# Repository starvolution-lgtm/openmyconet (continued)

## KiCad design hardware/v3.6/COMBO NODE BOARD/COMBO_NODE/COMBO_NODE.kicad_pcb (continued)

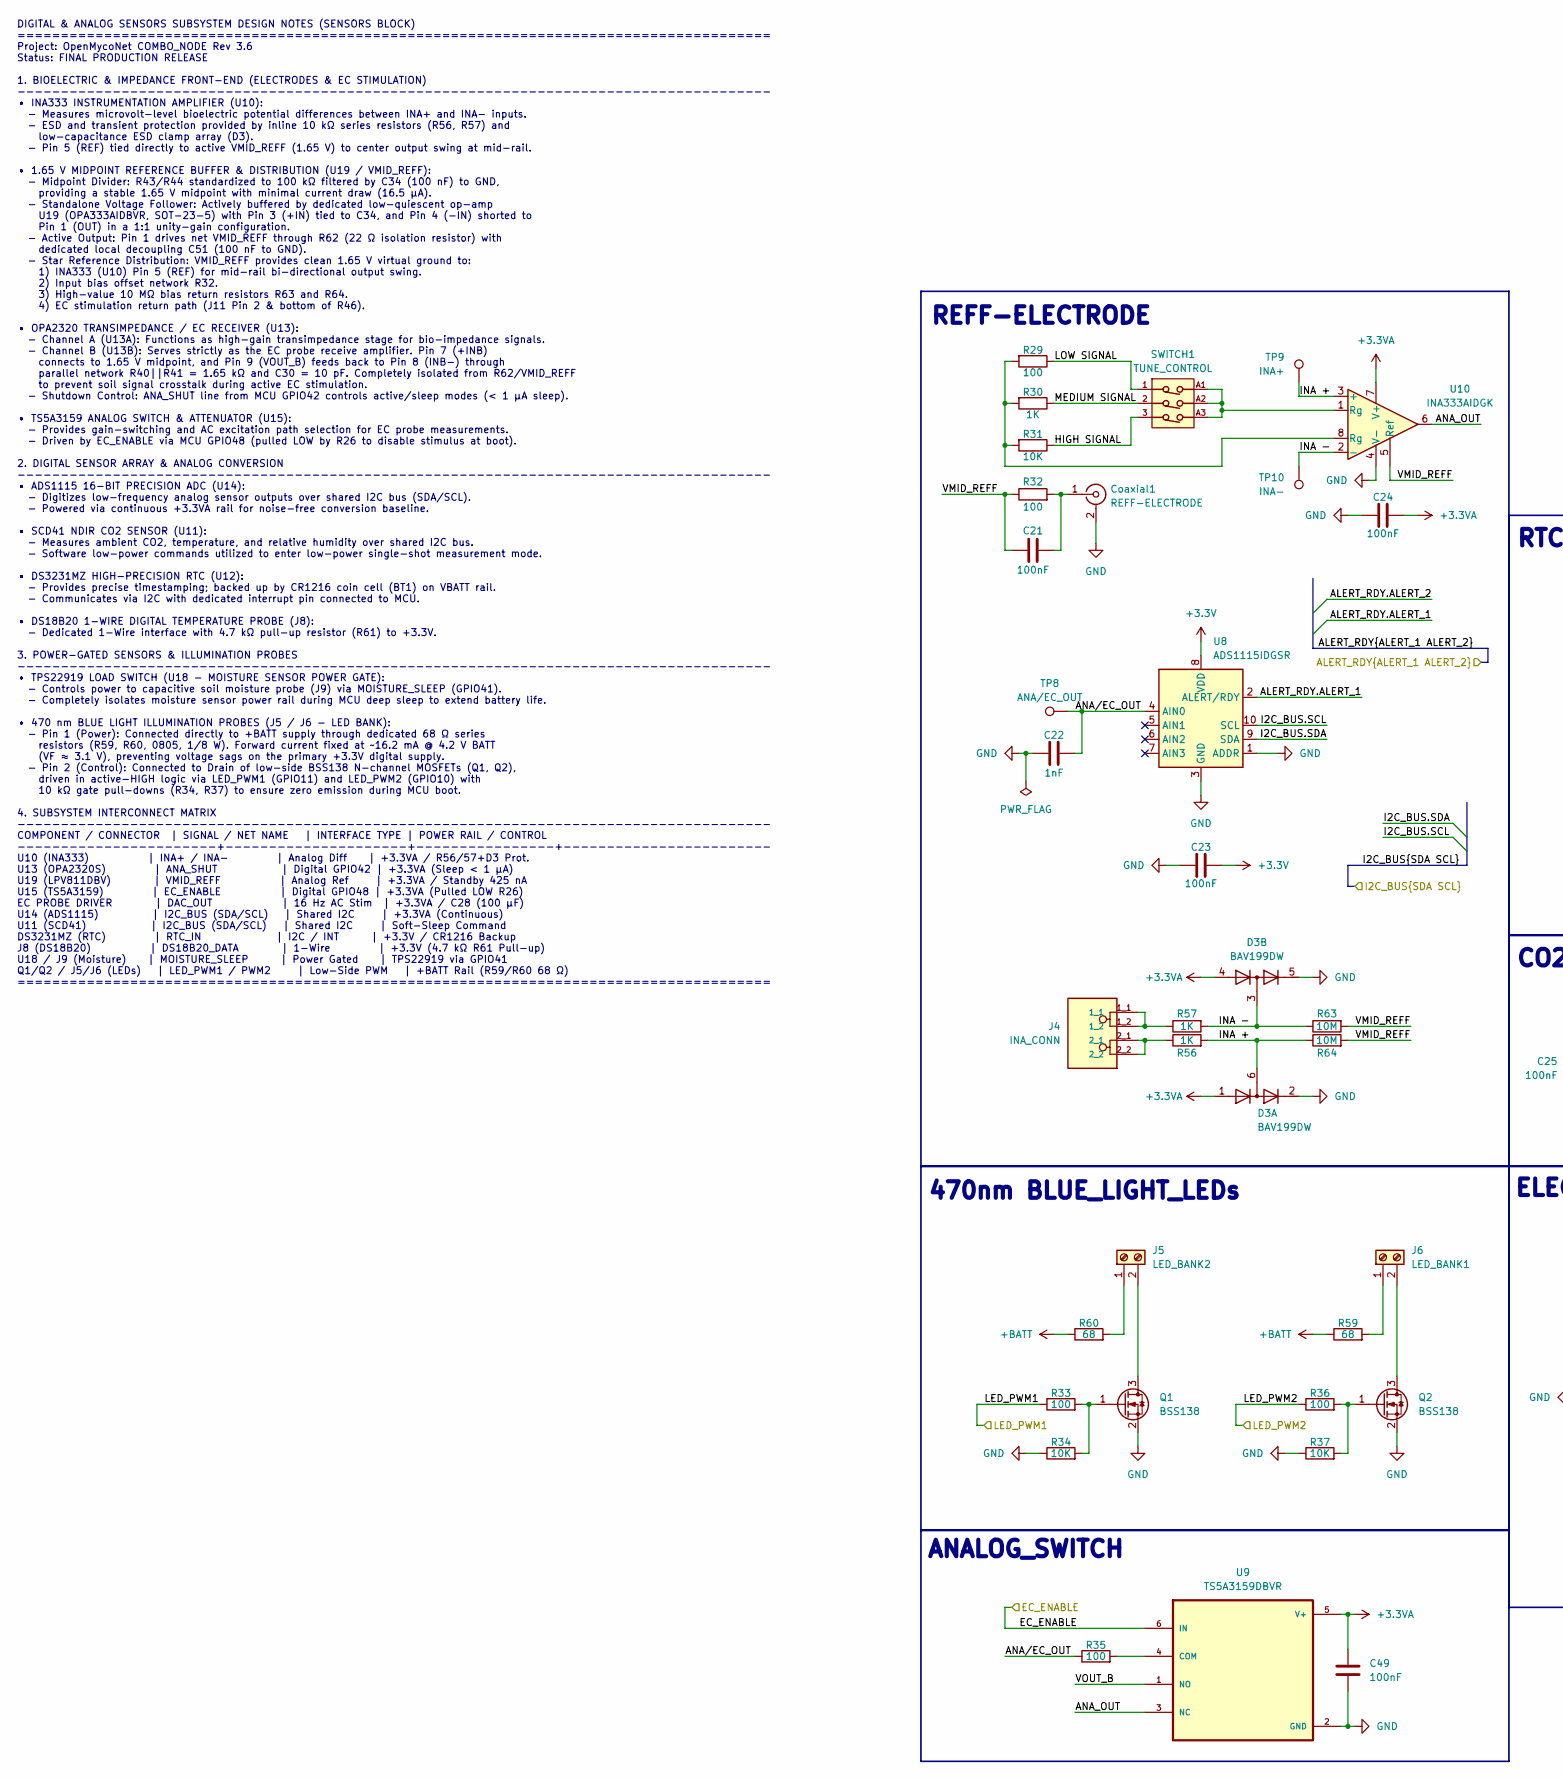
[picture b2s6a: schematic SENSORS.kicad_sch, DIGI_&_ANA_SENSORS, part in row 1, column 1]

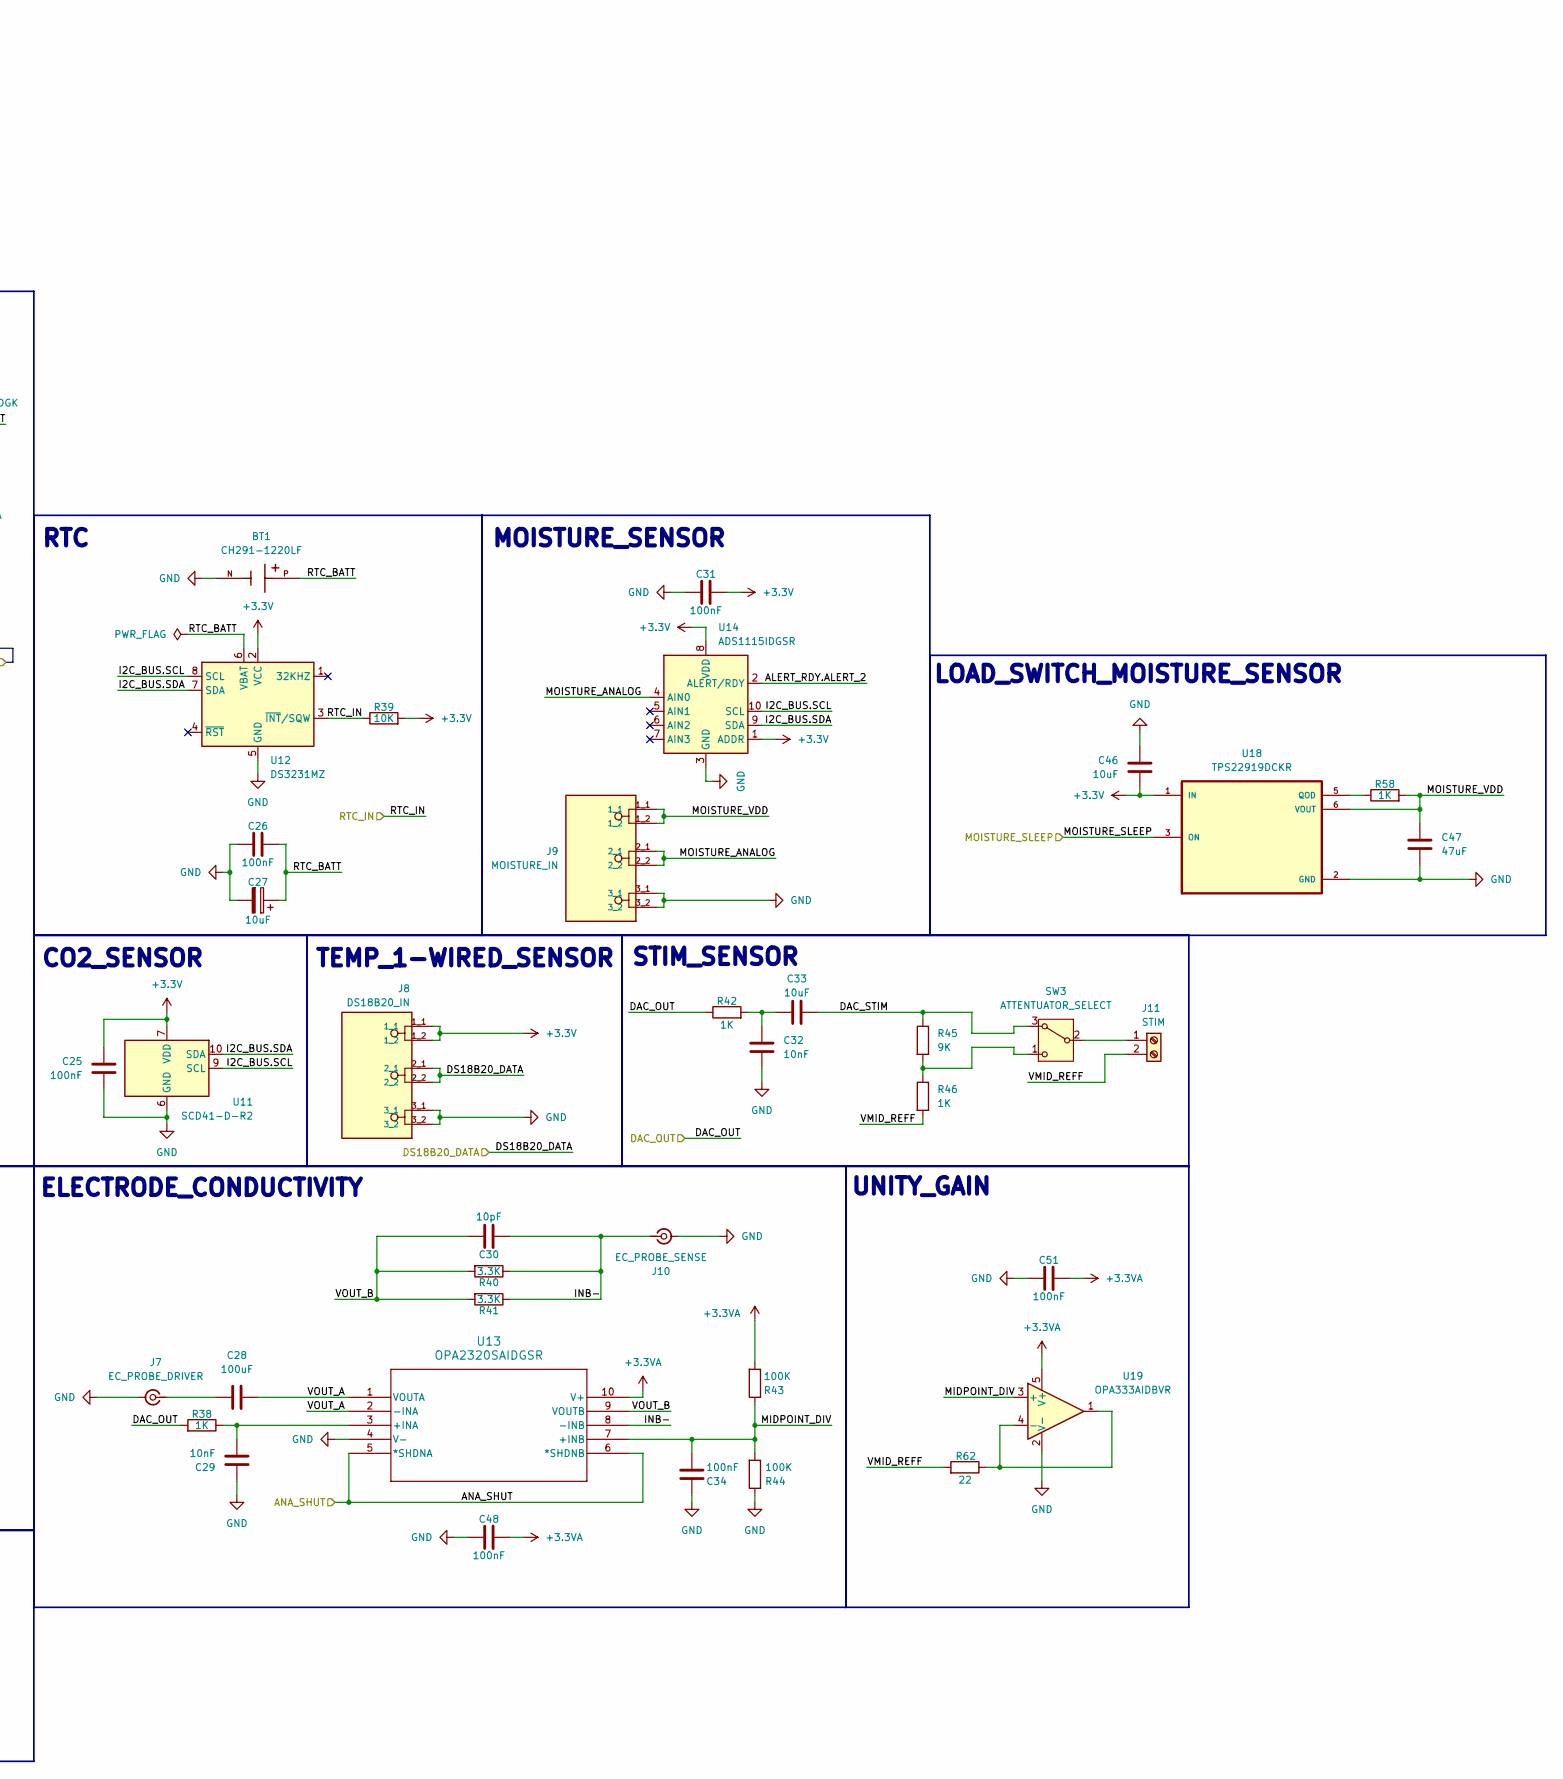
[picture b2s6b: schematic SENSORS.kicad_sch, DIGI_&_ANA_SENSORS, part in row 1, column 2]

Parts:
BT1: CH291-1220LF; BAT_CH291-1220LF; PARTREV A
C21, C25: 100nF; C_0805_2012Metric
C22: 1nF; C_0603_1608Metric
C23, C24, C26, C31, C34, C48, C49, C51: 100nF; C_0603_1608Metric
C27: 10uF; CP_EIA-3216-18_Kemet-A
C28: 100uF; C_1206_3216Metric
C29, C32: 10nF; C_0805_2012Metric
C30: 10pF; C_0603_1608Metric
C33: 10uF; C_0805_2012Metric
C46: 10uF; C_0603_1608Metric
C47: 47uF; C_0603_1608Metric
Coaxial1: REFF-ELECTRODE; CONN_73137-5003_MOL
D3: BAV199DW; SOT-363_SC-70-6
J4: INA_CONN; PHOENIX_1789618; PARTREV 25.11.2016
J5: LED_BANK2; TerminalBlock_Phoenix_MPT-0,5-2-2.54_1x02_P2.54mm_Horizontal
J6: LED_BANK1; TerminalBlock_Phoenix_MPT-0,5-2-2.54_1x02_P2.54mm_Horizontal
J7: EC_PROBE_DRIVER; CONN_73137-5003_MOL
J8: DS18B20_IN; PHOENIX_1790296
J9: MOISTURE_IN; PHOENIX_1790296
J10: EC_PROBE_SENSE; CONN_73137-5003_MOL
J11: STIM; TerminalBlock_Phoenix_MPT-0,5-2-2.54_1x02_P2.54mm_Horizontal
Q1, Q2: BSS138; SOT-23
R29, R32, R33, R36: 100; R_0805_2012Metric
R30, R42, R56, R57: 1K; R_0805_2012Metric
R31, R34, R37, R39: 10K; R_0805_2012Metric
R35: 100; R_0603_1608Metric
R38, R46, R58: 1K; R_0603_1608Metric
R40, R41: 3.3K; R_0603_1608Metric
R43, R44: 100K; R_0603_1608Metric
R45: 9K; R_0603_1608Metric
R59, R60: 68; R_0805_2012Metric
R62: 22; R_0603_1608Metric
R63, R64: 10M; R_0805_2012Metric
SW3: ATTENTUATOR_SELECT; SW_JS102011JCQN
SWITCH1: TUNE_CONTROL; 418117270903
TP8: ANA/EC_OUT; TestPoint_Loop_D1.80mm_Drill1.0mm_Beaded
TP9: INA+; TestPoint_Loop_D1.80mm_Drill1.0mm_Beaded
TP10: INA-; TestPoint_Loop_D1.80mm_Drill1.0mm_Beaded
U8, U14: ADS1115IDGSR; TSSOP-10_3x3mm_P0.5mm; LCSC C37593
U9: TS5A3159DBVR; SOT95P280X145-6N
U10: INA333AIDGK; VSSOP-8_3x3mm_P0.65mm
U11: SCD41-D-R2; Sensirion_SCD4x-1EP_10.1x10.1mm_P1.25mm_EP4.8x4.8mm
U12: DS3231MZ; SOIC-8_3.9x4.9mm_P1.27mm
U13: OPA2320SAIDGSR; DGS10_TEX
U18: TPS22919DCKR; SOT65P210X110-6N
U19: OPA333AIDBVR; SOT-23-5

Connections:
+3.3V: C23.1, C25.1, C31.1, C46.2, J8.1_1, J8.1_2, R39.2, U8.8 (VDD), U11.7 (VDD), U11.19 (VDD), U12.2 (VCC), U14.1 (ADDR), U14.8 (VDD), U18.1 (IN); also elsewhere on the board
+3.3VA: C24.1, C48.1, C49.1, C51.1, D3.1 (A1), D3.4 (A3), R43.2, U9.5 (V+), U10.7 (V+), U13.10 (V+), U19.5 (V+); also elsewhere on the board
+BATT: R59.1, R60.1; also elsewhere on the board
/BLOCK_DIAGRAM/BATTERY/I2C_BUS.SCL: U8.10 (SCL), U11.9 (SCL), U12.8 (SCL), U14.10 (SCL); also elsewhere on the board
/BLOCK_DIAGRAM/BATTERY/I2C_BUS.SDA: U8.9 (SDA), U11.10 (SDA), U12.7 (SDA), U14.9 (SDA); also elsewhere on the board
/BLOCK_DIAGRAM/DIGI_&_ANA_SENSORS/ALERT_RDY.ALERT_1: U8.2 (ALERT/RDY); also elsewhere on the board
/BLOCK_DIAGRAM/DIGI_&_ANA_SENSORS/ALERT_RDY.ALERT_2: U14.2 (ALERT/RDY); also elsewhere on the board
/BLOCK_DIAGRAM/DIGI_&_ANA_SENSORS/ANA_OUT: U9.3 (NC), U10.6
/BLOCK_DIAGRAM/DIGI_&_ANA_SENSORS/ANA_SHUT: U13.5 (*SHDNA), U13.6 (*SHDNB); also elsewhere on the board
/BLOCK_DIAGRAM/DIGI_&_ANA_SENSORS/ANA/EC_OUT: C22.2, R35.1, TP8.1 (1_1), U8.4 (AIN0)
/BLOCK_DIAGRAM/DIGI_&_ANA_SENSORS/DAC_OUT: R38.2, R42.1; also elsewhere on the board
/BLOCK_DIAGRAM/DIGI_&_ANA_SENSORS/DAC_STIM: C33.2, R45.1, SW3.3 (A)
/BLOCK_DIAGRAM/DIGI_&_ANA_SENSORS/DS18B20_DATA: J8.2_1, J8.2_2; also elsewhere on the board
/BLOCK_DIAGRAM/DIGI_&_ANA_SENSORS/EC_ENABLE: U9.6 (IN); also elsewhere on the board
/BLOCK_DIAGRAM/DIGI_&_ANA_SENSORS/HIGH SIGNAL: R31.1, SWITCH1.3
/BLOCK_DIAGRAM/DIGI_&_ANA_SENSORS/INA +: D3.6 (K3A4), R56.2, R64.1, TP9.1 (1_1), U10.3 (+)
/BLOCK_DIAGRAM/DIGI_&_ANA_SENSORS/INA -: D3.3 (K1A2), R57.2, R63.1, TP10.1 (1_1), U10.2 (-)
/BLOCK_DIAGRAM/DIGI_&_ANA_SENSORS/INB-: C30.1, J10.1 (In), R40.1, R41.1, U13.8 (-INB)
/BLOCK_DIAGRAM/DIGI_&_ANA_SENSORS/LED_PWM1: R33.1; also elsewhere on the board
/BLOCK_DIAGRAM/DIGI_&_ANA_SENSORS/LED_PWM2: R36.1; also elsewhere on the board
/BLOCK_DIAGRAM/DIGI_&_ANA_SENSORS/LOW SIGNAL: R29.1, SWITCH1.1
/BLOCK_DIAGRAM/DIGI_&_ANA_SENSORS/MEDIUM SIGNAL: R30.1, SWITCH1.2
/BLOCK_DIAGRAM/DIGI_&_ANA_SENSORS/MIDPOINT_DIV: C34.2, R43.1, R44.2, U13.7 (+INB), U19.3 (+)
/BLOCK_DIAGRAM/DIGI_&_ANA_SENSORS/MOISTURE_ANALOG: J9.2_1, J9.2_2, U14.4 (AIN0)
/BLOCK_DIAGRAM/DIGI_&_ANA_SENSORS/MOISTURE_SLEEP: U18.3 (ON); also elsewhere on the board
/BLOCK_DIAGRAM/DIGI_&_ANA_SENSORS/MOISTURE_VDD: C47.1, J9.1_1, J9.1_2, R58.2, U18.6 (VOUT)
/BLOCK_DIAGRAM/DIGI_&_ANA_SENSORS/RTC_BATT: BT1.P, C26.2, C27.1, U12.6 (VBAT)
/BLOCK_DIAGRAM/DIGI_&_ANA_SENSORS/RTC_IN: R39.1, U12.3 (~INT/SQW); also elsewhere on the board
/BLOCK_DIAGRAM/DIGI_&_ANA_SENSORS/VMID_REFF: C21.1, J11.2, R32.1, R46.2, R62.2, R63.2, R64.2, U10.5 (Ref)
/BLOCK_DIAGRAM/DIGI_&_ANA_SENSORS/VOUT_A: C28.1, U13.1 (VOUTA), U13.2 (-INA)
/BLOCK_DIAGRAM/DIGI_&_ANA_SENSORS/VOUT_B: C30.2, R40.2, R41.2, U9.1 (NO), U13.9 (VOUTB)
GND: BT1.N, C22.1, C23.2, C24.2, C25.2, C26.1, C27.2, C29.1, C31.2, C32.2, C34.1, C46.1, C47.2, C48.2, C49.2, C51.2, Coaxial1.2 (Ext), D3.2 (K2), D3.5 (K4), J7.2 (Ext), J8.3_1, J8.3_2, J9.3_1, J9.3_2, J10.2 (Ext), Q1.2 (S), Q2.2 (S), R34.1, R37.1, R44.1, U8.1 (ADDR), U8.3 (GND), U9.2 (GND), U10.4 (V-), U11.6 (GND), U11.20 (GND), U11.21 (GND), U12.5 (GND), U13.4 (V-), U14.3 (GND), U18.2 (GND), U19.2 (V-); also elsewhere on the board
unnamed: C32.1, C33.1, R42.2
unnamed: C21.2, Coaxial1.1 (In), R32.2
unnamed: J4.1_1, J4.1_2, R57.1
unnamed: J4.2_1, J4.2_2, R56.1
unnamed: J5.1, R60.2
unnamed: J5.2, Q1.3 (D)
unnamed: J6.1, R59.2
unnamed: J6.2, Q2.3 (D)
unnamed: C28.2, J7.1 (In)
unnamed: J11.1, SW3.2 (B)
unnamed: Q1.1 (G), R33.2, R34.2
unnamed: Q2.1 (G), R36.2, R37.2
unnamed: R29.2, R30.2, R31.2, U10.8 (Rg)
unnamed: R45.2, R46.1, SW3.1 (C)
unnamed: SWITCH1.A1, SWITCH1.A2, SWITCH1.A3, U10.1 (Rg)
unnamed: R35.2, U9.4 (COM)
unnamed: C29.2, R38.1, U13.3 (+INA)
unnamed: R58.1, U18.5 (QOD)
unnamed: R62.1, U19.1, U19.4 (-)

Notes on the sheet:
ELECTRODE_CONDUCTIVITY
ANALOG_SWITCH
UNITY_GAIN
CO2_SENSOR
TEMP_1-WIRED_SENSOR
MOISTURE_SENSOR
STIM_SENSOR
RTC
LOAD_SWITCH_MOISTURE_SENSOR
REFF-ELECTRODE
DIGITAL & ANALOG SENSORS SUBSYSTEM DESIGN NOTES (SENSORS BLOCK) ======================================================================================= Project: OpenMycoNet COMBO_NODE Rev 3.6 Status: FINAL PRODUCTION RELEASE 1. BIOELECTRIC & IMPEDANCE FRONT-END (ELECTRODES & EC STIMULATION) -------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
470nm BLUE_LIGHT_LEDs

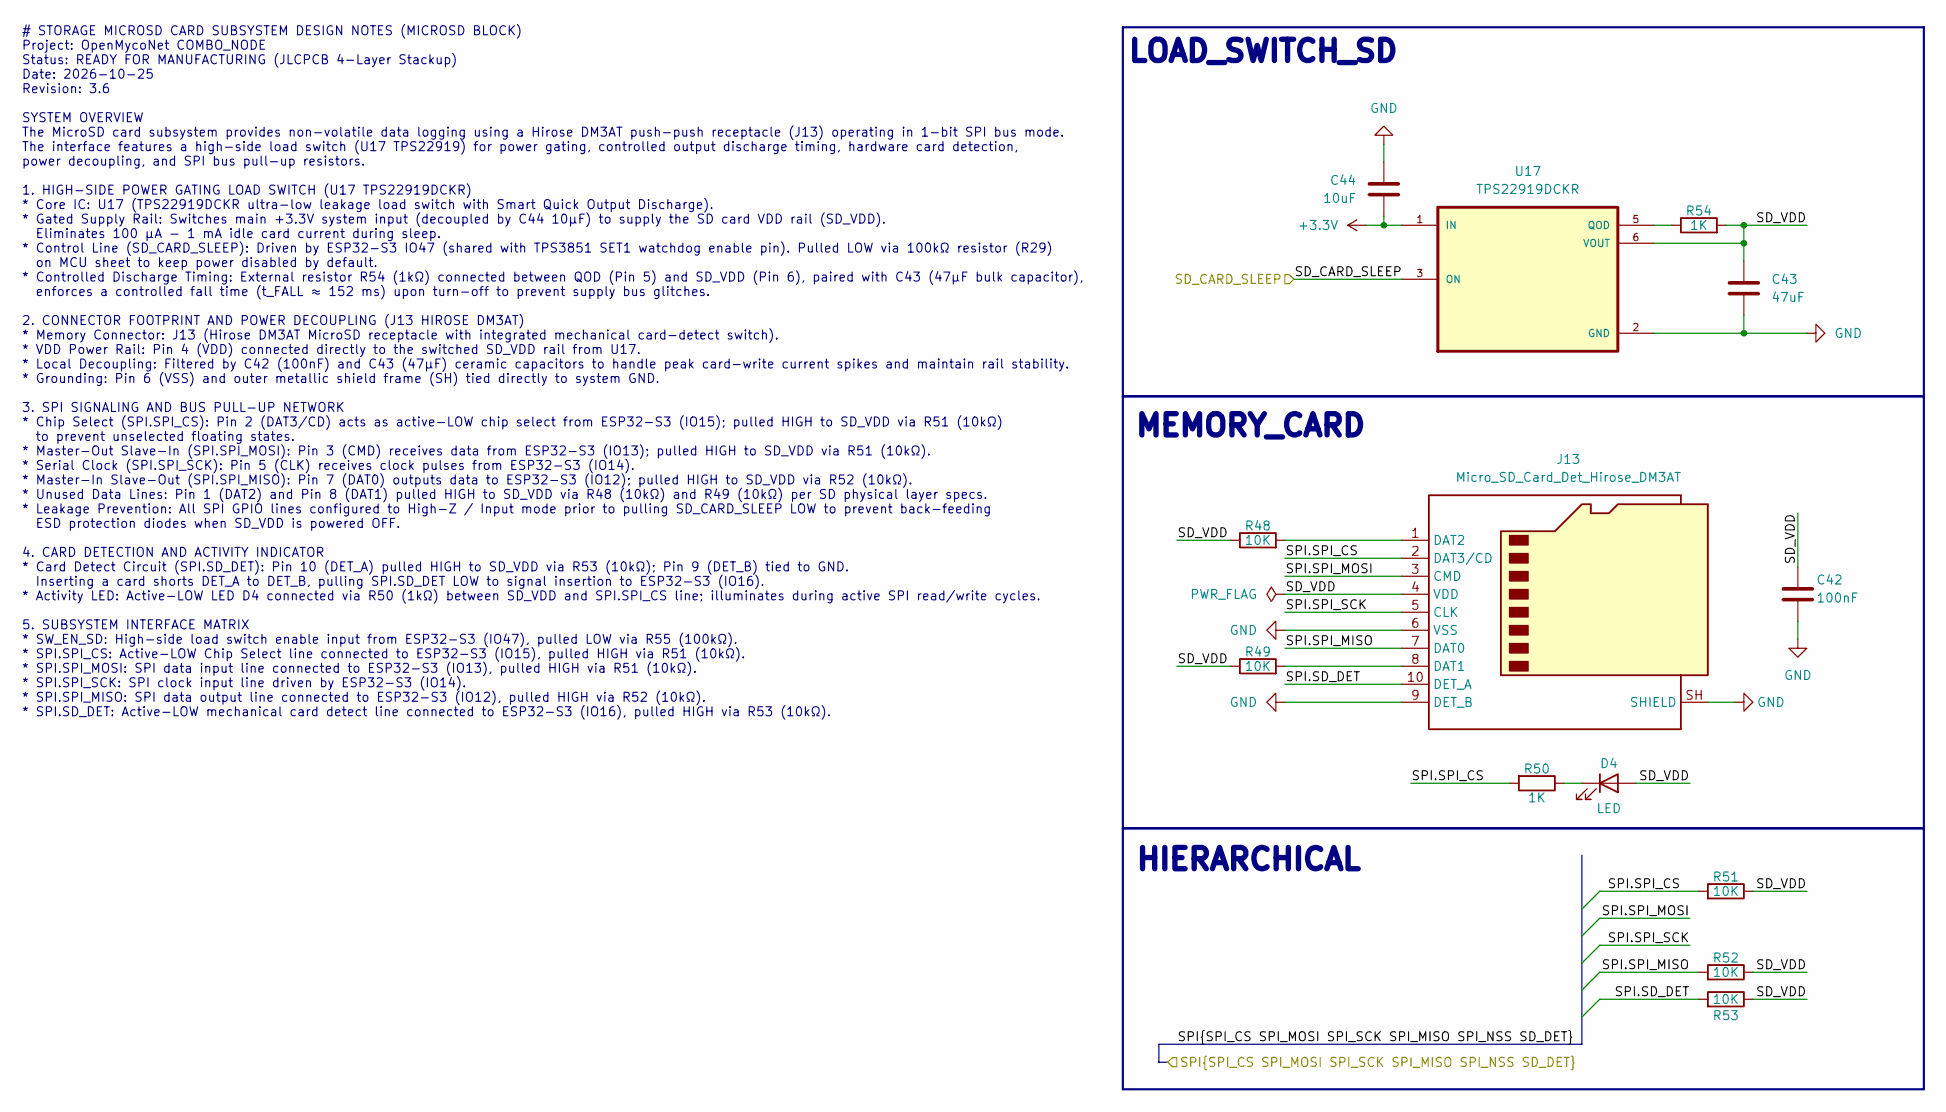
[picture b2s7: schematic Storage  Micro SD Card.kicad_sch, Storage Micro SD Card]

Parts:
C42: 100nF; C_0603_1608Metric
C43: 47uF; C_0603_1608Metric
C44: 10uF; C_0603_1608Metric
D4: LED; LED_0603_1608Metric
J13: Micro_SD_Card_Det_Hirose_DM3AT; microSD_HC_Hirose_DM3AT-SF-PEJM5
R48, R49, R51, R52, R53: 10K; R_0603_1608Metric
R50, R54: 1K; R_0603_1608Metric
U17: TPS22919DCKR; SOT65P210X110-6N

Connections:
+3.3V: C44.2, U17.1 (IN); also elsewhere on the board
/BLOCK_DIAGRAM/LoRa/SPI.SD_DET: J13.10 (DET_A), R53.2; also elsewhere on the board
/BLOCK_DIAGRAM/LoRa/SPI.SPI_CS: J13.2 (DAT3/CD), R50.2, R51.2; also elsewhere on the board
/BLOCK_DIAGRAM/LoRa/SPI.SPI_MISO: J13.7 (DAT0), R52.2; also elsewhere on the board
/BLOCK_DIAGRAM/LoRa/SPI.SPI_MOSI: J13.3 (CMD); also elsewhere on the board
/BLOCK_DIAGRAM/LoRa/SPI.SPI_SCK: J13.5 (CLK); also elsewhere on the board
/BLOCK_DIAGRAM/MCU/SD_CARD_SLEEP: U17.3 (ON); also elsewhere on the board
/BLOCK_DIAGRAM/Storage Micro SD Card/SD_VDD: C42.1, C43.1, D4.2 (A), J13.4 (VDD), R48.1, R49.1, R51.1, R52.1, R53.1, R54.2, U17.6 (VOUT)
GND: C42.2, C43.2, C44.1, J13.6 (VSS), J13.9 (DET_B), J13.SH (SHIELD), U17.2 (GND); also elsewhere on the board
unnamed: D4.1 (K), R50.1
unnamed: J13.8 (DAT1), R49.2
unnamed: J13.1 (DAT2), R48.2
unnamed: R54.1, U17.5 (QOD)

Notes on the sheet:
HIERARCHICAL
MEMORY_CARD
LOAD_SWITCH_SD
# STORAGE MICROSD CARD SUBSYSTEM DESIGN NOTES (MICROSD BLOCK) Project: OpenMycoNet COMBO_NODE Status: READY FOR MANUFACTURING (JLCPCB 4-Layer Stackup) Date: 2026-10-25 Revision: 3.6 SYSTEM OVERVIEW The MicroSD card subsystem provides non-volatile data logging using a Hirose DM3AT push-push receptac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

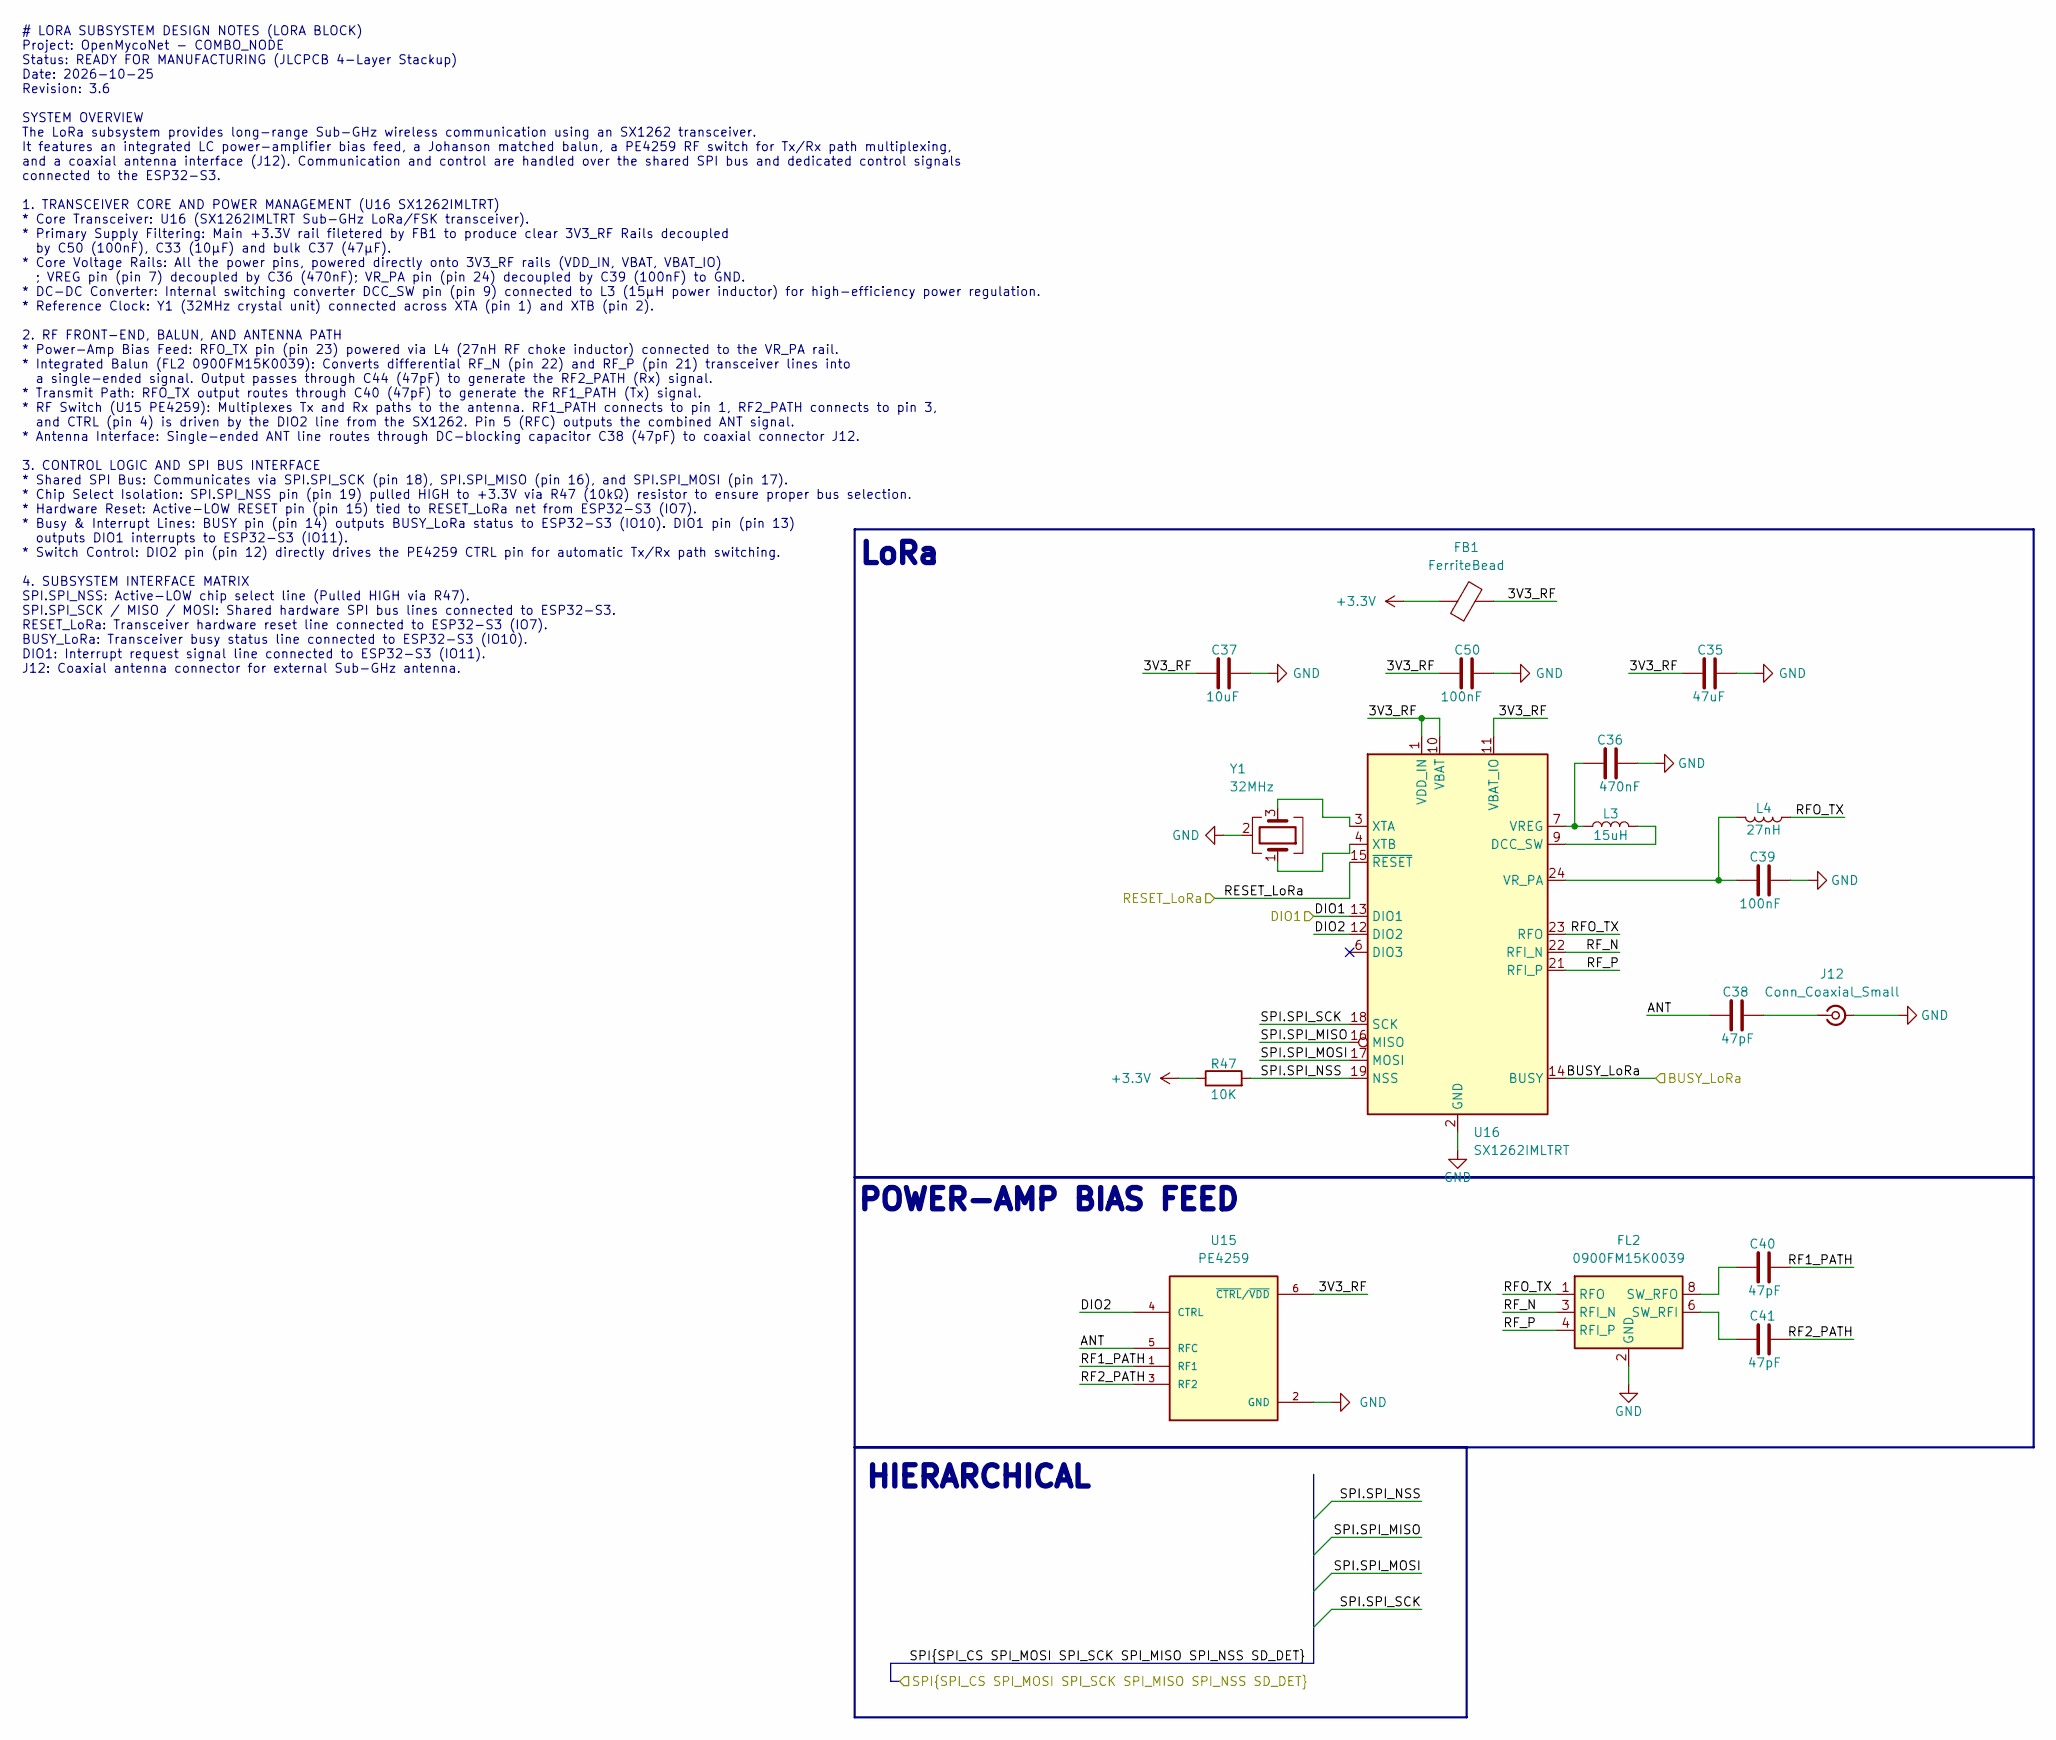
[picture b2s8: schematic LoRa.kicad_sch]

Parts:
C35: 47uF; C_1206_3216Metric
C36: 470nF; C_1206_3216Metric
C37: 10uF; C_1206_3216Metric
C38, C40, C41: 47pF; C_0805_2012Metric
C39, C50: 100nF; C_0805_2012Metric
FB1: FerriteBead; L_0603_1608Metric
FL2: 0900FM15K0039; Balun_Johanson_0900FM15K0039
J12: Conn_Coaxial_Small; U.FL_Hirose_U.FL-R-SMT-1_Vertical
L3: 15uH; L_APV_APH1040
L4: 27nH; L_0603_1608Metric
R47: 10K; R_0603_1608Metric
U15: PE4259; SOT65P215X110-6N
U16: SX1262IMLTRT; QFN-24-1EP_4x4mm_P0.5mm_EP2.6x2.6mm
Y1: 32MHz; Crystal_SMD_2520-4Pin_2.5x2.0mm

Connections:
+3.3V: FB1.1, R47.1; also elsewhere on the board
/BLOCK_DIAGRAM/LoRa/3V3_RF: C35.1, C37.1, C50.1, FB1.2, U15.6 (~CTRL/~VDD), U16.1 (VDD_IN), U16.10 (VBAT), U16.11 (VBAT_IO)
/BLOCK_DIAGRAM/LoRa/ANT: C38.1, U15.5 (RFC)
/BLOCK_DIAGRAM/LoRa/BUSY_LoRa: U16.14 (BUSY); also elsewhere on the board
/BLOCK_DIAGRAM/LoRa/DIO1: U16.13 (DIO1); also elsewhere on the board
/BLOCK_DIAGRAM/LoRa/DIO2: U15.4 (CTRL), U16.12 (DIO2)
/BLOCK_DIAGRAM/LoRa/RESET_LoRa: U16.15 (~RESET); also elsewhere on the board
/BLOCK_DIAGRAM/LoRa/RF1_PATH: C40.2, U15.1 (RF1)
/BLOCK_DIAGRAM/LoRa/RF2_PATH: C41.2, U15.3 (RF2)
/BLOCK_DIAGRAM/LoRa/RFO_TX: FL2.1 (RFO), L4.1, U16.23 (RFO)
/BLOCK_DIAGRAM/LoRa/RF_N: FL2.3 (RFI_N), U16.22 (RFI_N)
/BLOCK_DIAGRAM/LoRa/RF_P: FL2.4 (RFI_P), U16.21 (RFI_P)
/BLOCK_DIAGRAM/LoRa/SPI.SPI_MISO: U16.16 (MISO); also elsewhere on the board
/BLOCK_DIAGRAM/LoRa/SPI.SPI_MOSI: U16.17 (MOSI); also elsewhere on the board
/BLOCK_DIAGRAM/LoRa/SPI.SPI_NSS: R47.2, U16.19 (NSS); also elsewhere on the board
/BLOCK_DIAGRAM/LoRa/SPI.SPI_SCK: U16.18 (SCK); also elsewhere on the board
GND: C35.2, C36.1, C37.2, C39.2, C50.2, FL2.2 (GND), FL2.5 (GND), FL2.7 (GND), FL2.9 (GND), FL2.10 (GND), J12.2 (Ext), U15.2 (GND), U16.2 (GND), U16.5 (GND), U16.8 (GND), U16.20 (GND), U16.25 (GND), Y1.2 (G), Y1.4 (G); also elsewhere on the board
unnamed: C41.1, FL2.6 (SW_RFI)
unnamed: C40.1, FL2.8 (SW_RFO)
unnamed: C38.2, J12.1 (In)
unnamed: L3.2, U16.9 (DCC_SW)
unnamed: C36.2, L3.1, U16.7 (VREG)
unnamed: C39.1, L4.2, U16.24 (VR_PA)
unnamed: U16.3 (XTA), Y1.3
unnamed: U16.4 (XTB), Y1.1

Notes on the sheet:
# LORA SUBSYSTEM DESIGN NOTES (LORA BLOCK) Project: OpenMycoNet - COMBO_NODE Status: READY FOR MANUFACTURING (JLCPCB 4-Layer Stackup) Date: 2026-10-25 Revision: 3.6 SYSTEM OVERVIEW The LoRa subsystem provides long-range Sub-GHz wireless communication using an SX1262 transceiver. It features an inte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
LoRa
HIERARCHICAL
POWER-AMP BIAS FEED

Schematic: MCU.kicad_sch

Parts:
C14, C15, C16, C18, C19, C20, C45: 100nF; C_0603_1608Metric
C17: 10uF; CP_EIA-3216-18_Kemet-A
J3: EXPANSIONS; PinHeader_2x05_P2.54mm_Vertical_SMD
R17, R18, R61: 4.7K; R_0603_1608Metric
R19, R20, R21, R22, R23, R24, R25, R26, R27, R28: 10K; R_0603_1608Metric
R55, R65: 100K; R_0603_1608Metric
SW1: RESET; SW_SPST_B3U-1000P
SW2: BOOT0; SW_SPST_B3U-1000P
U6: ESP32-S3-WROOM-1-N16R8; ESP32-S3-WROOM-1
U7: TPS3851H33EDRBR; IC_DRV8601DRBT

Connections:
+3.3V: C14.1, C15.1, C16.1, C17.1, C45.1, J3.7, J3.9, R17.1, R18.1, R19.1, R20.1, R21.1, R22.1, R27.1, R28.1, R61.1, R65.2, U6.2 (3V3), U7.1 (VDD); also elsewhere on the board
/BLOCK_DIAGRAM/BATTERY/BATT_ALERT: R20.2, U6.23 (IO21); also elsewhere on the board
/BLOCK_DIAGRAM/BATTERY/I2C_BUS.SCL: J3.1, R17.2, U6.12 (IO8); also elsewhere on the board
/BLOCK_DIAGRAM/BATTERY/I2C_BUS.SDA: J3.2, R18.2, U6.17 (IO9); also elsewhere on the board
/BLOCK_DIAGRAM/DIGI_&_ANA_SENSORS/ALERT_RDY.ALERT_1: R21.2, U6.31 (IO38); also elsewhere on the board
/BLOCK_DIAGRAM/DIGI_&_ANA_SENSORS/ALERT_RDY.ALERT_2: R22.2, U6.32 (IO39); also elsewhere on the board
/BLOCK_DIAGRAM/DIGI_&_ANA_SENSORS/ANA_SHUT: R23.2, U6.35 (IO42); also elsewhere on the board
/BLOCK_DIAGRAM/DIGI_&_ANA_SENSORS/DAC_OUT: U6.38 (IO2); also elsewhere on the board
/BLOCK_DIAGRAM/DIGI_&_ANA_SENSORS/DS18B20_DATA: R61.2, U6.6 (IO6); also elsewhere on the board
/BLOCK_DIAGRAM/DIGI_&_ANA_SENSORS/EC_ENABLE: R26.2, U6.25 (IO48); also elsewhere on the board
/BLOCK_DIAGRAM/DIGI_&_ANA_SENSORS/LED_PWM1: U6.11 (IO18); also elsewhere on the board
/BLOCK_DIAGRAM/DIGI_&_ANA_SENSORS/LED_PWM2: U6.10 (IO17); also elsewhere on the board
/BLOCK_DIAGRAM/DIGI_&_ANA_SENSORS/MOISTURE_SLEEP: U6.34 (IO41); also elsewhere on the board
/BLOCK_DIAGRAM/DIGI_&_ANA_SENSORS/RTC_IN: U6.5 (IO5); also elsewhere on the board
/BLOCK_DIAGRAM/LoRa/BUSY_LoRa: U6.18 (IO10); also elsewhere on the board
/BLOCK_DIAGRAM/LoRa/DIO1: U6.19 (IO11); also elsewhere on the board
/BLOCK_DIAGRAM/LoRa/RESET_LoRa: U6.7 (IO7); also elsewhere on the board
/BLOCK_DIAGRAM/LoRa/SPI.SD_DET: U6.9 (IO16); also elsewhere on the board
/BLOCK_DIAGRAM/LoRa/SPI.SPI_CS: U6.8 (IO15); also elsewhere on the board
/BLOCK_DIAGRAM/LoRa/SPI.SPI_MISO: J3.5, U6.20 (IO12); also elsewhere on the board
/BLOCK_DIAGRAM/LoRa/SPI.SPI_MOSI: J3.3, U6.21 (IO13); also elsewhere on the board
/BLOCK_DIAGRAM/LoRa/SPI.SPI_NSS: U6.39 (IO1); also elsewhere on the board
/BLOCK_DIAGRAM/LoRa/SPI.SPI_SCK: J3.4, U6.22 (IO14); also elsewhere on the board
/BLOCK_DIAGRAM/MCU/BOOT0: C19.2, R28.2, SW2.1, U6.27 (IO0)
/BLOCK_DIAGRAM/MCU/RESET: C18.2, R27.2, SW1.1, U7.3 (~MR)
/BLOCK_DIAGRAM/MCU/RESET_CHIP: U6.3 (EN), U7.8 (~RESET)
/BLOCK_DIAGRAM/MCU/RST_WDI: U6.4 (IO4), U7.6 (WDI)
/BLOCK_DIAGRAM/MCU/SD_CARD_SLEEP: U6.33 (IO40); also elsewhere on the board
/BLOCK_DIAGRAM/MCU/UART_RX: J3.8, U6.36 (RXD0)
/BLOCK_DIAGRAM/MCU/UART_TX: J3.10, U6.37 (TXD0)
/BLOCK_DIAGRAM/MCU/USB_DATA.USB_D+: U6.14 (USB_D+); also elsewhere on the board
/BLOCK_DIAGRAM/MCU/USB_DATA.USB_D-: U6.13 (USB_D-); also elsewhere on the board
/BLOCK_DIAGRAM/MCU/WCD_SLEEP: R55.2, U6.24 (IO47), U7.5 (SET1)
GND: C14.2, C15.2, C16.2, C17.2, C18.1, C19.1, C20.2, C45.2, J3.6, R23.1, R24.1, R25.1, R26.1, R55.1, SW1.2, SW2.2, U6.1 (GND), U6.40 (GND), U6.41 (GND), U7.4 (GND), U7.9 (EXP), U7.10 (EXP), U7.11 (EXP), U7.12 (EXP), U7.13 (EXP); also elsewhere on the board
unnamed: R19.2, U6.15 (IO3)
unnamed: R24.2, U6.26 (IO45)
unnamed: R25.2, U6.16 (IO46)
unnamed: C20.1, U7.2 (CWD)
unnamed: R65.1, U7.7 (~WDO)

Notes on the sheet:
# MCU SUBSYSTEM DESIGN NOTES (MCU BLOCK) Project: OpenMycoNet COMBO_NODE Status: READY FOR MANUFACTURING (JLCPCB 4-Layer Stackup) Date: 2026-10-25 Revision: 3.6 --- ### SYSTEM OVERVIEW The MCU subsystem centers on the ESP32-S3-WROOM-1-N16R8 module (U6) operating from a regulated +3.3V digital suppl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
MCU
PUSH-BUTTON
EXPANSIONs
HIERARCHICAL
WATCHDOG

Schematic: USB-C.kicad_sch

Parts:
C1: 100nF; C_0603_1608Metric
D1: SMBJ5.0A; PARTREV F2102
D2: SS34; D_SMA
FL1: BLM18PG121SN1D; BEADC1608X95N
J1: USB_C_Receptacle_USB2.0_16P; USB_C_Receptacle_GCT_USB4105-xx-A_16P_TopMnt_Horizontal
R1, R2: 5.1K; R_0402_1005Metric
R3, R4: 27; R_0402_1005Metric
U1: USBLC6-2SC6

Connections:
/BLOCK_DIAGRAM/MCU/USB_DATA.USB_D+: R4.2; also elsewhere on the board
/BLOCK_DIAGRAM/MCU/USB_DATA.USB_D-: R3.2; also elsewhere on the board
/BLOCK_DIAGRAM/USB-C/D+: J1.A6 (D+), J1.B6 (D+), U1.3
/BLOCK_DIAGRAM/USB-C/D-: J1.A7 (D-), J1.B7 (D-), U1.1
/BLOCK_DIAGRAM/USB-C/USB: C1.1, D1.C, FL1.1, J1.A4 (VBUS), J1.A9 (VBUS), J1.B4 (VBUS), J1.B9 (VBUS)
GND: C1.2, D1.A, J1.A1 (GND), J1.A12 (GND), J1.B1 (GND), J1.B12 (GND), J1.SH (SHIELD), R1.2, R2.2, U1.2; also elsewhere on the board
unnamed: D2.2 (A), FL1.2
unnamed: J1.A5 (CC1), R1.1
unnamed: J1.B5 (CC2), R2.1
unnamed: R3.1, U1.6
unnamed: R4.1, U1.4
VBUS: D2.1 (K), U1.5; also elsewhere on the board

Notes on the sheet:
ESD_PROTECTION
USB-C INTERFACE DESIGN NOTES (REVISED V3.6) Project: OpenMycoNet - COMBO_NODE Status: READY FOR MANUFACTURING (JLCPCB 4-Layer Stackup) Date: 2026-10-25 Revision: 3.6 SYSTEM TOPOLOGY Connector: J1 (USB-C 16-Pin Receptacle, USB 2.0 Full-Speed Only). Configuration: Upstream Facing Port (UFP) device mo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
USB-C
